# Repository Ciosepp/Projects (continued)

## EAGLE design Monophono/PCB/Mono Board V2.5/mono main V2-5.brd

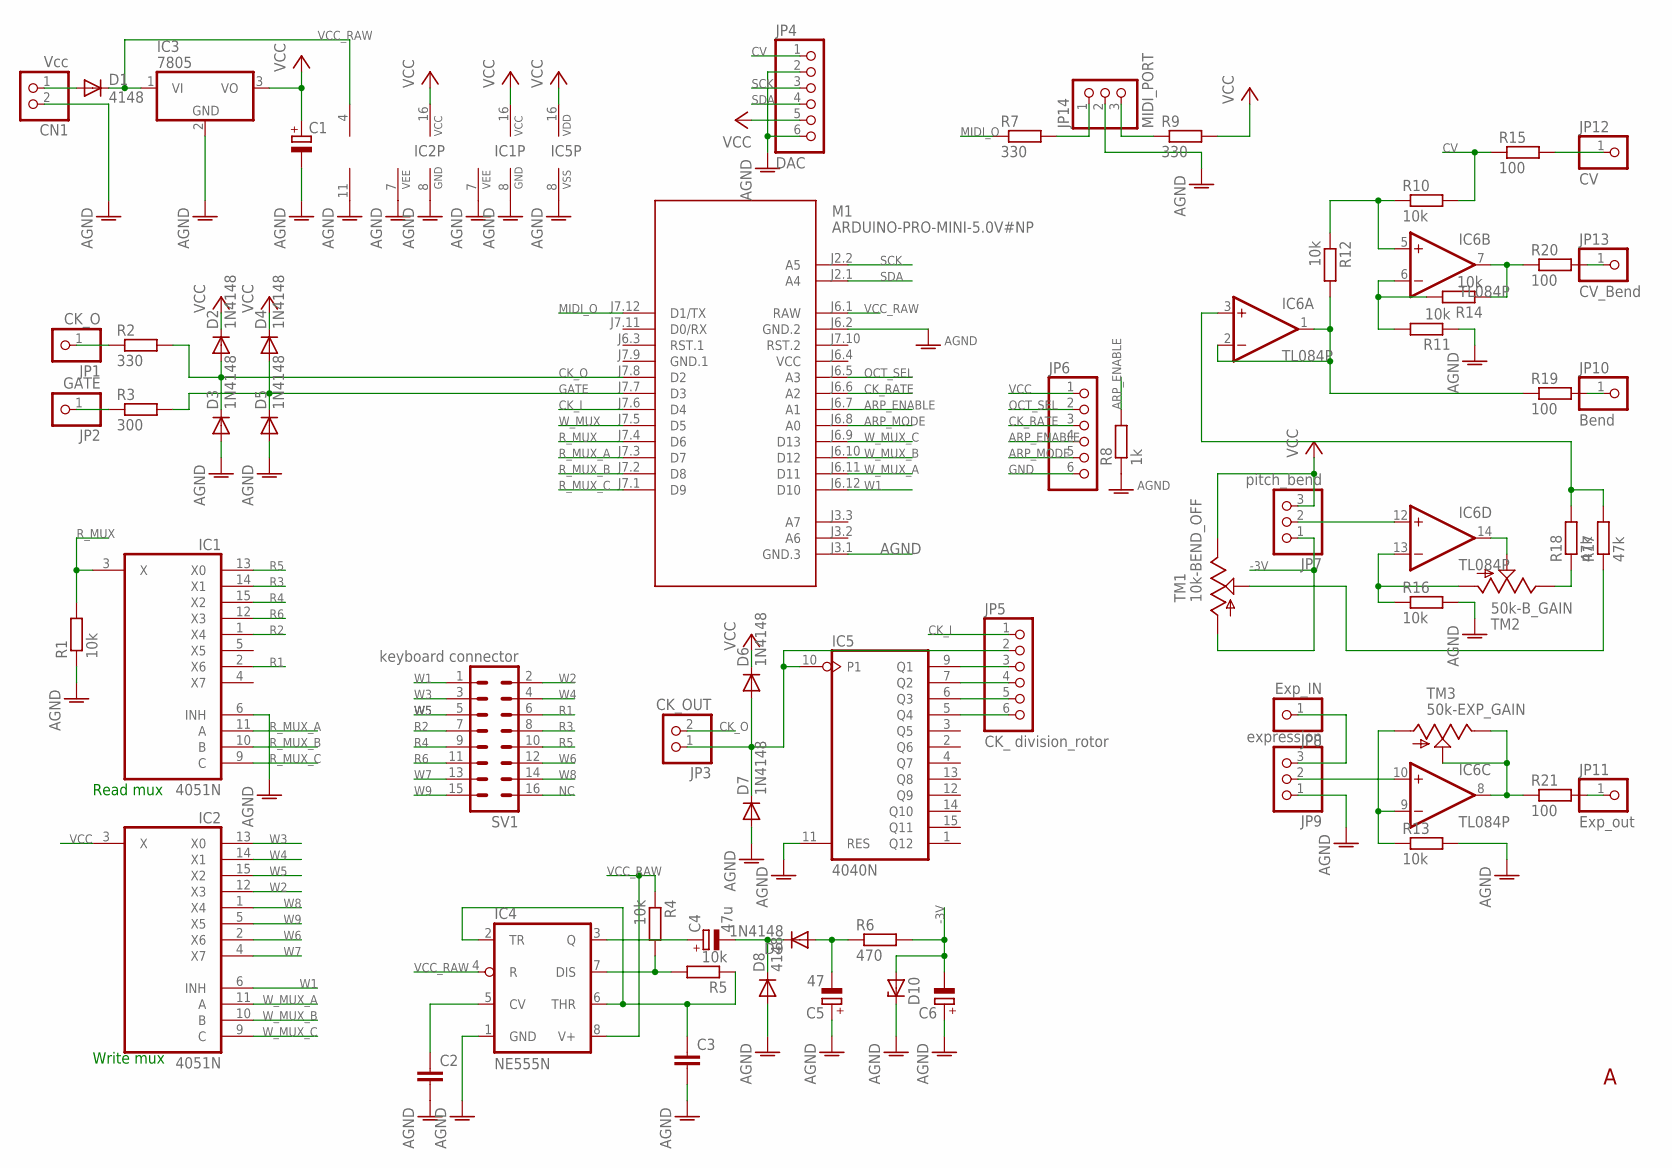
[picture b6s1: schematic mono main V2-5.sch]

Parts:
C1, C6: CPOL-EUE5-8.5; E5-8,5
C2, C3: C-EU050-030X075; C050-030X075
C4: 47u; E5-8,5
C5: 47; E5-8,5
CN1: Vcc; JST-PH-2-THM
D1, D8: 4148; D-2.5
D2, D3, D6, D7, D9: 1N4148; D-2.5
D4, D5: 1N4148; DO35-7
D10: ZENER-DIODEZD-7.5; ZDIO-7.5
IC1, IC2: 4051N; DIL16
IC3: 7805; TO220V
IC4: NE555N; DIL08-ROUND
IC5: 4040N; DIL16
IC6: TL084P; DIL14
JP1: CK_O; 1X01
JP2: GATE; 1X01
JP3: CK_OUT; 1X02
JP4: DAC; 1X06
JP5: CK_ division_rotor; 1X06
JP6: PINHD-1X6; 1X06
JP7: pitch_bend; 1X03
JP8: Exp_IN; 1X01
JP9: expression; 1X03
JP10: Bend; 1X01
JP11: Exp_out; 1X01
JP12: CV; 1X01
JP13: CV_Bend; 1X01
JP14: MIDI_PORT; 1X03
M1: ARDUINO-PRO-MINI-5.0V#NP; ARDUINO-PRO-MINI#NP
R1, R12: 10k; 0204/7
R2, R7, R9: 330; 0204V
R3: 300; 0204V
R4, R5, R10, R11, R13, R14, R16: 10k; 0204V
R6: 470; 0204V
R8: 1k; 0204/7
R15, R19, R20, R21: 100; 0204V
R17: 47k; 0204V
R18: 47k; 0204/7
SV1: keyboard connector; MA08-2
TM1: 10k-BEND_OFF; 6MM
TM2: 50k-B_GAIN; 6MM
TM3: 50k-EXP_GAIN; 6MM

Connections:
-3V: C6.-, D10.A, JP7.1, R6.2, TM1.A
AGND: C1.-, C2.2, C3.2, C5.+, C6.+, CN1.2 (1), D3.A, D5.A, D7.A, D8.A, D10.C, IC1.6 (INH), IC1.7 (VEE), IC1.8 (GND), IC2.7 (VEE), IC2.8 (GND), IC3.2 (GND), IC4.1 (GND), IC5.8 (VSS), IC5.11 (RES), IC6.11 (V-), JP4.2, JP4.6, JP9.1, JP14.2, M1.J3.1 (GND.3), M1.J6.2 (GND.2), R1.1, R8.1, R11.1, R13.2, R16.2
ARP_ENABLE: JP6.4, M1.J6.7 (A1), R8.2
ARP_MODE: JP6.5, M1.J6.8 (A0)
CK_I: JP5.1, M1.J7.6 (D4)
CK_O: D2.A, D3.C, JP3.2, M1.J7.8 (D2), R2.2
CK_RATE: JP6.3, M1.J6.6 (A2)
CV: JP4.1, R10.2, R15.1
GATE: D4.A, D5.C, M1.J7.7 (D3), R3.2
GND: JP6.6
GND.1: M1.J7.9 (GND.1)
MIDI_O: M1.J7.12 (D1/TX), R7.1
unnamed: IC6.14 (OUT), TM2.S
unnamed: R17.1, TM1.S
unnamed: R18.1, TM2.E
unnamed: IC6.3 (+IN), R17.2, R18.2
unnamed: IC6.1 (OUT), IC6.2 (-IN), R12.2, R19.1
unnamed: JP10.1, R19.2
unnamed: JP13.1, R20.2
unnamed: JP11.1, R21.2
unnamed: JP12.1, R15.2
unnamed: JP1.1, R2.1
unnamed: IC5.9 (Q1), JP5.3
unnamed: IC5.7 (Q2), JP5.4
unnamed: IC5.6 (Q3), JP5.5
unnamed: IC5.5 (Q4), JP5.6
unnamed: D6.A, D7.C, IC5.10 (P1), JP3.1, JP5.2
unnamed: JP2.1, R3.1
unnamed: JP14.1, R7.2
unnamed: JP14.3, R9.1
unnamed: IC6.9 (-IN), R13.1, TM3.A
unnamed: IC4.7 (DIS), R4.2, R5.2
unnamed: C3.1, IC4.2 (TR), IC4.6 (THR), R5.1
unnamed: C2.1, IC4.5 (CV)
unnamed: C4.+, IC4.3 (Q)
unnamed: C4.-, D8.C, D9.C
unnamed: C5.-, D9.A, R6.1
unnamed: IC6.12 (+IN), JP7.2
unnamed: IC6.13 (-IN), R16.1, TM2.A
unnamed: IC6.10 (+IN), JP9.2
unnamed: IC6.8 (OUT), R21.1, TM3.E, TM3.S
unnamed: CN1.1 (2), D1.A
unnamed: IC6.6 (-IN), R11.2, R14.2
unnamed: IC6.7 (OUT), R14.1, R20.1
unnamed: IC6.5 (+IN), R10.1, R12.1
unnamed: JP8.1, JP9.3
NC: SV1.16
OCT_SEL: JP6.2, M1.J6.5 (A3)
R1: IC1.2 (X6), SV1.6
R2: IC1.1 (X4), SV1.7
R3: IC1.14 (X1), SV1.8
R4: IC1.15 (X2), SV1.9
R5: IC1.13 (X0), SV1.10
R6: IC1.12 (X3), SV1.11
R_MUX: IC1.3 (X), M1.J7.4 (D6), R1.2
R_MUX_A: IC1.11 (A), M1.J7.3 (D7)
R_MUX_B: IC1.10 (B), M1.J7.2 (D8)
R_MUX_C: IC1.9 (C), M1.J7.1 (D9)
SCK: JP4.3, M1.J2.2 (A5)
SDA: JP4.4, M1.J2.1 (A4)
VCC: C1.+, D2.C, D4.C, D6.C, IC1.16 (VCC), IC2.3 (X), IC2.16 (VCC), IC3.3 (VO), IC5.16 (VDD), JP4.5, JP6.1, JP7.3, M1.J6.4 (VCC), R9.2, TM1.E
VCC_RAW: D1.C, IC3.1 (VI), IC4.4 (R), IC4.8 (V+), IC6.4 (V+), M1.J6.1 (RAW), R4.1
W1: IC2.6 (INH), M1.J6.12 (D10), SV1.1
W2: IC2.12 (X3), SV1.2
W3: IC2.13 (X0), SV1.3
W4: IC2.14 (X1), SV1.4
W5: IC2.15 (X2), SV1.5
W6: IC2.2 (X6), SV1.12
W7: IC2.4 (X7), SV1.13
W8: IC2.1 (X4), SV1.14
W9: IC2.5 (X5), SV1.15
W_MUX: M1.J7.5 (D5)
W_MUX_A: IC2.11 (A), M1.J6.11 (D11)
W_MUX_B: IC2.10 (B), M1.J6.10 (D12)
W_MUX_C: IC2.9 (C), M1.J6.9 (D13)

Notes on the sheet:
Read mux
Write mux

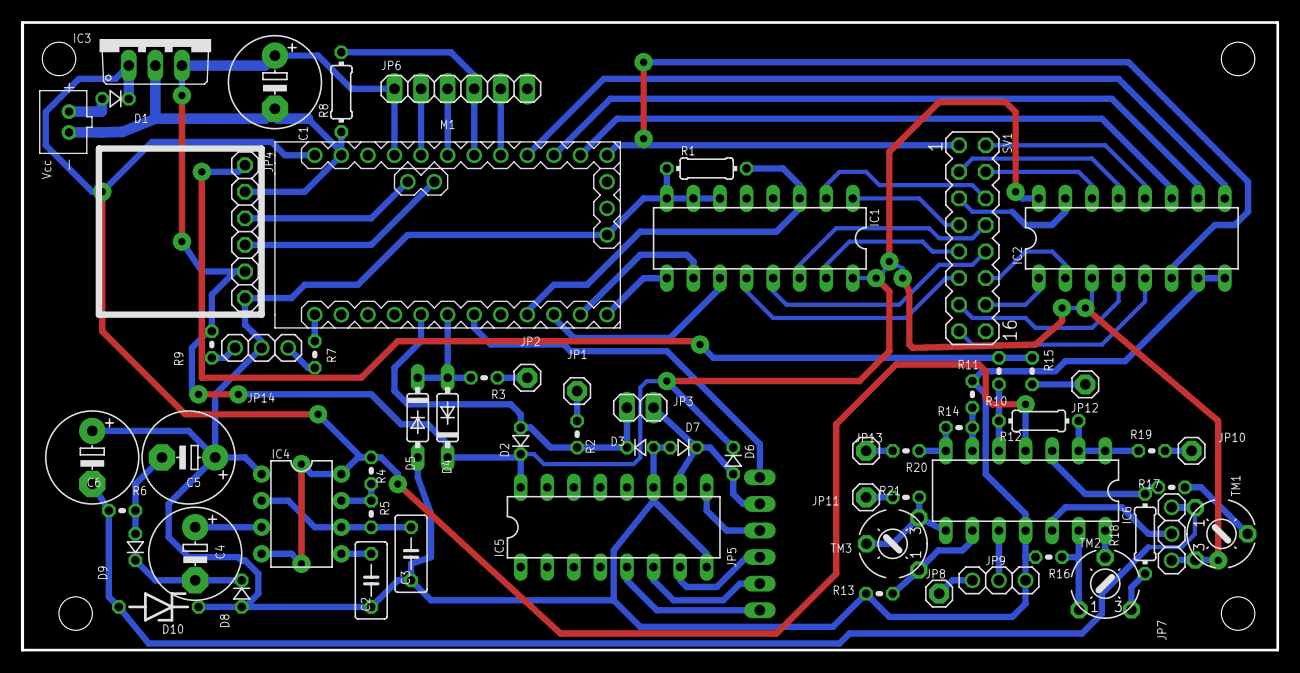
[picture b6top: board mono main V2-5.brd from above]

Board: 2 copper layers, 120.0 x 60.0 mm, 63 parts (1 on the bottom side), 71 nets.

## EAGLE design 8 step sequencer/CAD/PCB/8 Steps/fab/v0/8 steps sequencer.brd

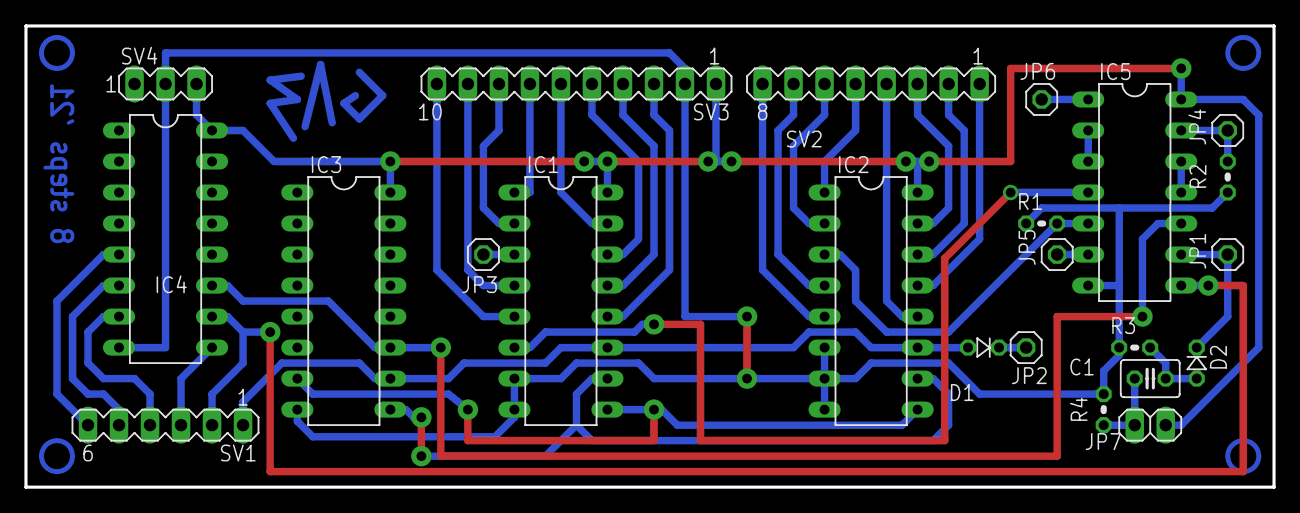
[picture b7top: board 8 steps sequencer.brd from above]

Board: 2 copper layers, 102.2 x 37.8 mm, 23 parts (0 on the bottom side), 39 nets.

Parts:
C1: C025-030X050
D1, D2: 1N4148; D-2.5
IC1, IC2: 4051N; DIL16
IC3, IC4: 4040N; DIL16
IC5: 40106N; DIL14
JP1: CK_IN; 1X01
JP2: CK_OUT; 1X01
JP3: CV_OUT; 1X01
JP4: RESET; 1X01
JP5: GATE_OUT; 1X01
JP6: CV_silencer; 1X01
JP7: STEP; 1X02
R1: 10k; 0204V
R2: 1k; 0204V
R3, R4: 0204V
SV1: DIV_SEL; MA06-1
SV2: GATE_SWS; MA08-1
SV3: POTS; MA10-1
SV4: PWR; MA03-1

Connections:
GND: IC1.7, IC1.8, IC2.6, IC2.7, IC2.8, IC3.8, IC4.8, IC5.7, R1.1, R2.1, R3.1, R4.1, SV3.2, SV4.2
unnamed: D2.C, IC5.9, JP1.1
unnamed: IC4.10, IC5.8, SV1.2
unnamed: IC4.9, SV1.3
unnamed: IC4.7, SV1.4
unnamed: IC4.6, SV1.5
unnamed: IC4.5, SV1.6
unnamed: IC2.13, SV2.1
unnamed: D1.A, IC1.11, IC2.11, IC3.10, SV1.1
unnamed: IC1.10, IC2.10, IC3.9
unnamed: IC1.9, IC2.9, IC3.7
unnamed: IC2.14, SV2.2
unnamed: IC2.15, SV2.3
unnamed: IC2.12, SV2.4
unnamed: IC2.1, SV2.5
unnamed: IC2.5, SV2.8
unnamed: IC2.2, SV2.6
unnamed: IC2.4, SV2.7
unnamed: IC1.1, SV3.7
unnamed: IC1.2, SV3.8
unnamed: IC1.4, SV3.9
unnamed: IC1.5, SV3.10
unnamed: IC1.15, SV3.6
unnamed: IC1.14, SV3.5
unnamed: IC1.13, SV3.4
unnamed: IC1.12, SV3.3
unnamed: IC1.3, JP3.1
unnamed: IC5.11, IC5.12
unnamed: IC5.13, JP4.1, R2.2
unnamed: IC2.3, IC5.5, R1.2
unnamed: D1.C, JP2.1
unnamed: IC5.2, IC5.3
unnamed: IC5.6, JP5.1
unnamed: IC5.1, JP6.1
unnamed: IC1.6, IC5.4
unnamed: C1.2, JP7.1, R4.2
unnamed: C1.1, D2.A, R3.2
unnamed: IC3.11, IC4.11, IC5.10
VCC: IC1.16, IC2.16, IC3.16, IC4.16, IC5.14, JP7.2, SV3.1, SV4.3

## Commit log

2022-04-08 First project
    added folder hierarchy and first files of 8 step project
2022-04-09 Added Wire cutter project
    Src not finished yet!!!
2022-04-11 added blank file
2022-04-11 Added new Timer Arduino library
2022-04-16 Added laminator source code
2022-04-16 Removed Laminator project (now it's grown, it has its own repo)
2022-06-06 monooo
2022-07-04 Ready
2022-07-17 eagle 8 steps
2022-08-04 new fabrication files of 8 steps
2022-08-25 finalization
2022-08-27 Auto stash before rebase of "origin/main"
2022-12-12 modifying stuff
2023-01-05 RevB added
